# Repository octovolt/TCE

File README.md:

TCE: Two Comparator Effect
===

This is a Eurorack version of the [two_comparator_effect](https://github.com/cyberboy666/two_comparator_effect) originally designed by [Rob Schafer](https://www.youtube.com/c/schaferob) and later improved by [cyberboy666](https://github.com/cyberboy666). I communicated with cyberboy666 before publishing this module and received his blessing to do so.

The circuit compares the voltage of a composite video signal to two different threshold voltages to produce two binary signals. That is, if the video signal is brighter than the threshold, the output is "high" or white. If the video signal is darker than the threshold, the output is "low" or black. One of the binary signals is sent out at a lower voltage level than the other, so the mixed output of both signals is white, gray and black.

A [demo video](https://youtu.be/mtZ2dQ727Hc) is available if you would like to see the module in action. The video shows a version that used tall trimmer pots instead of the more robust Alpha 9mm pots in the BOM, but it is otherwise identical. 

The LM339 Comparator
--------------------

It's worth noting that this circuit uses an LM339 comparator, which is not quite fast enough for video. The LM339 has a response time of about 1.3 microseconds, and we really need a response time below 83 nanoseconds for video. As a result, the resulting video image is slightly shifted to the right. This is not an issue unless your are mixing the output with the original signal in some way. Even then, the offset sort of looks interesting. I will say this for the LM339: it's very cheap, easy to find, and it comes in a quad through-hole package. Unfortunately, with the way through-hole components are going extinct, there aren't a lot of other great options in a quad package.

Build Guide
-----------

When soldering, please also see the [interactive BOM](https://octovolt.github.io/TCE). After soldering a component, make sure to trim the excess leads as much as possible. This is particularly important where the potentiometers sit over the top of solder pads for other components.

Steps:

1. Solder all resistors and the D1 diode on the primary, back side of the circuit board (the side with the open source hardware logo). I call this the back side because it faces away from the front panel. D1 says 1N914 on the BOM but this can be replaced by a 1N4148 or 1N5819. I use a 1N4148 in all of my builds. Make sure to get the polarity correct when you place diodes! The line on the circuit board should match the stripe on the diode.
2. Solder the diodes and ferrite beads on the front side of the board. D2 and D3 are the standard Eurorack reverse polarity protection diodes. I use 1N4004, but you can use any diode in the 1N400x series. Once again, do make sure to get the polarity correct when you place the diodes.
3. Solder the ceramic capacitors on the back side of the board.
4. Solder the socket for the IC, if you want to one. People say it introduces extra capacitance, but it's probably no big deal in this circuit. A socket will protect the IC and make it reusable in other projects.
5. Solder the transistor and voltage regulators (U2, U3, Q1). Make sure they are facing the correct direction as indicated on the circuit board.
6. Solder the power headers. Please note that a shrouded, keyed power header will be very slightly too wide for a 4hp module (fractions of a millimeter) so you should probably use normal header pins here. The PCB is marked to indicate where the -12v (red stripe) of the power cable should go.
7. Solder the electrolytic capacitors. Mind the polarity -- the white side of the circle on the circuit board is the negative side of the capacitor.
8. Place but do not solder the jacks, knobs and switch on the front side of circuit board.
9. Place the front panel over the jacks, knobs and switch, and then use their nuts to attach them to the front panel.
10. Solder the jacks, knobs and switch.
11. If you used an IC socket, put the IC in the socket. If you did not use a socket, solder the IC now. Mind the polarity -- the small semi-circle on the board should match the notch on the IC.
12. Test and enjoy!

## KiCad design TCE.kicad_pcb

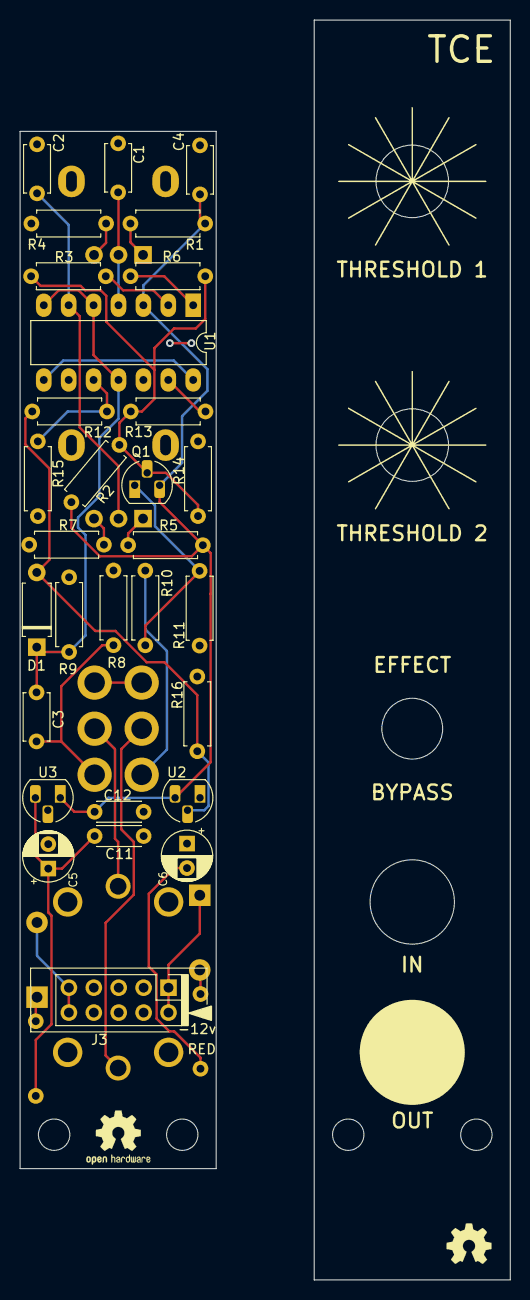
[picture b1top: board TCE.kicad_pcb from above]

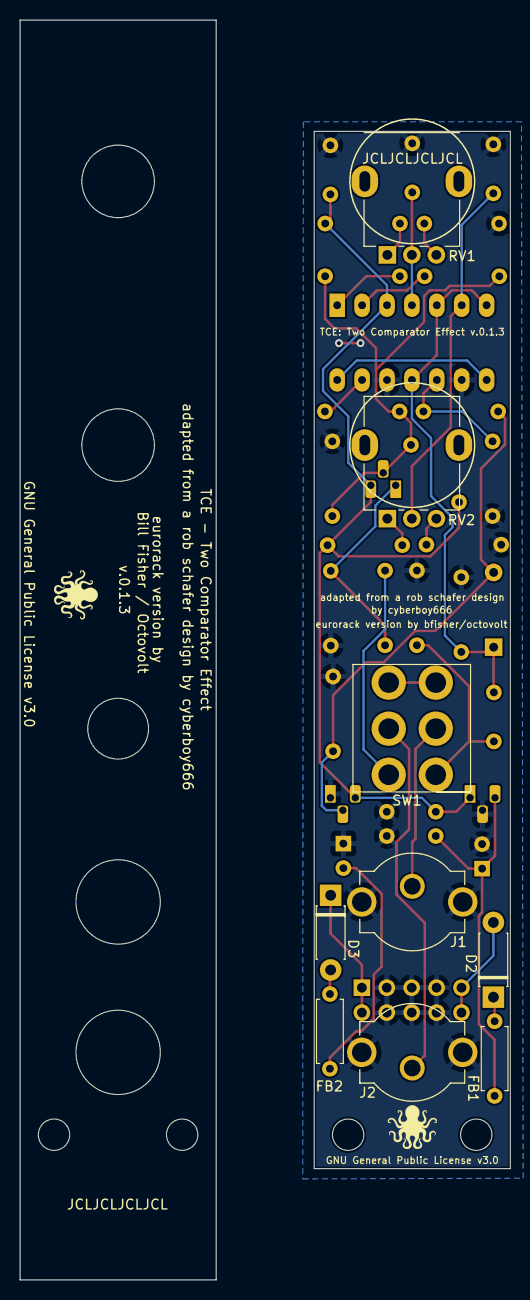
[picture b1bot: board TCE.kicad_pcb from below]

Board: 2 copper layers, 20.0 x 105.8 mm, 41 parts (11 on the bottom side), 28 nets.

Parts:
C1, C2, C3: 1u; C_Disc_D4.7mm_W2.5mm_P5.00mm
C4: 0.1u; C_Disc_D4.7mm_W2.5mm_P5.00mm
C5, C6: 10u; CP_Radial_D5.0mm_P2.50mm
C11: .33u; C_Disc_D4.3mm_W1.9mm_P5.00mm
C12: 0.1u; C_Disc_D4.3mm_W1.9mm_P5.00mm
D1: 1n914; D_A-405_P7.62mm_Horizontal
D2, D3: 1n4007; D_DO-41_SOD81_P7.62mm_Horizontal
FB1, FB2: Ferrite Bead; R_Axial_DIN0207_L6.3mm_D2.5mm_P7.62mm_Horizontal
J1, J2: rca; tht_vertical_rca
J3: europower; PinHeader_2x05_P2.54mm_Vertical
Q1: 2N3904; TO-92_HandSolder
R1, R5: 3k; R_Axial_DIN0207_L6.3mm_D2.5mm_P7.62mm_Horizontal
R2, R15: 1k; R_Axial_DIN0207_L6.3mm_D2.5mm_P7.62mm_Horizontal
R3: 1.2k; R_Axial_DIN0207_L6.3mm_D2.5mm_P7.62mm_Horizontal
R4, R7: 910; R_Axial_DIN0207_L6.3mm_D2.5mm_P7.62mm_Horizontal
R6: 680; R_Axial_DIN0207_L6.3mm_D2.5mm_P7.62mm_Horizontal
R8, R10: 75; R_Axial_DIN0207_L6.3mm_D2.5mm_P7.62mm_Horizontal
R9: 150k; R_Axial_DIN0207_L6.3mm_D2.5mm_P7.62mm_Horizontal
R11: 47; R_Axial_DIN0207_L6.3mm_D2.5mm_P7.62mm_Horizontal
R12: 470; R_Axial_DIN0207_L6.3mm_D2.5mm_P7.62mm_Horizontal
R13: 180; R_Axial_DIN0207_L6.3mm_D2.5mm_P7.62mm_Horizontal
R14: 1.5k; R_Axial_DIN0207_L6.3mm_D2.5mm_P7.62mm_Horizontal
R16: 100; R_Axial_DIN0207_L6.3mm_D2.5mm_P7.62mm_Horizontal
RV1, RV2: 1k_pot; Potentiometer_Alpha_RD901F-40-00D_Single_Vertical
Ref**: Val**; octopus_silk_screen
Ref**#2: Val**; octopus_silk_screen
SW1: SW_DPDT_x2; dpdt_mini_toggle_switch_tayda
U1: LM339; DIP-14_W7.62mm_LongPads
U2: LM317; TO-92_HandSolder
U3: L78L05; TO-92_HandSolder

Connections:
+1.25V: D1.2 (A), R12.2, R16.1, U2.2 (VO)
+5V: C4.1, C12.1, Q1.3 (C), R1.1, R2.1, R5.1, U1.3 (V+), U2.3 (VI), U3.1 (VO)
+12V: C5.1, C11.1, FB1.2, U3.3 (VI)
-12V: C6.2, FB2.2
GND: C1.1, C2.1, C4.2, C5.2, C6.1, C11.2, C12.2, J1.2 (Ext), J2.2 (Ext), J3.3, J3.4, J3.5, J3.6, J3.7, J3.8, R4.1, R7.1, R8.2, R9.2, R11.2, R14.1, R15.1, R16.2, U1.9 (+), U1.12 (V-), U2.1 (ADJ), U3.2 (GND)
unnamed: C3.2, R8.1, SW1.3 (C)
unnamed: D2.1 (K), FB1.1
unnamed: D2.2 (A), J3.9, J3.10
unnamed: D3.1 (K), J3.1, J3.2
unnamed: D3.2 (A), FB2.1
unnamed: J1.1 (In), SW1.2 (B)
unnamed: J2.1 (In), SW1.5 (B)
unnamed: Q1.2 (B), R2.2, R3.2, R6.2, R13.2, R14.2
unnamed: R1.2, RV1.1
unnamed: R3.1, U1.2
unnamed: R4.2, RV1.3
unnamed: R5.2, RV2.1
unnamed: R6.1, U1.1
unnamed: R7.2, RV2.3
unnamed: R10.2, SW1.6 (C)
unnamed: R12.1, R15.2, U1.10 (-)
unnamed: R13.1, U1.13
unnamed: SW1.1 (A), SW1.4 (A)
unnamed: U1.8 (-), U1.14
THRESHOLD_1: C1.2, RV1.2, U1.4 (-)
THRESHOLD_2: C2.2, RV2.2, U1.6 (-)
VIDEO_IN: C3.1, D1.1 (K), R9.1, U1.5 (+), U1.7 (+), U1.11 (+)
VIDEO_OUT: Q1.1 (E), R10.1, R11.1

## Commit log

2023-12-31 interactive bom on docs branch
2023-12-31 change name of git pages directory to docs
2023-12-31 revise interactive bom
2023-12-31 add link to interactive bom
2023-12-31 add 3D rendering to README.md
2023-12-31 Update README.md again
2023-12-31 Update build guide
2023-12-31 .gitignore, image of pcb/panel, shift C3 slightly
2023-12-31 2nd 3D rendering, changes to silkscreen text
2023-12-31 2nd 3d rendering in README.md
2024-01-16 Update README.md regarding the power pins

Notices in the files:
TCE.kicad_pcb:
GNU General Public License v3.0
